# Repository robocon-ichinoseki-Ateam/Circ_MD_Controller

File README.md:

# MD_Controller
VNH5019を駆動させるための回路

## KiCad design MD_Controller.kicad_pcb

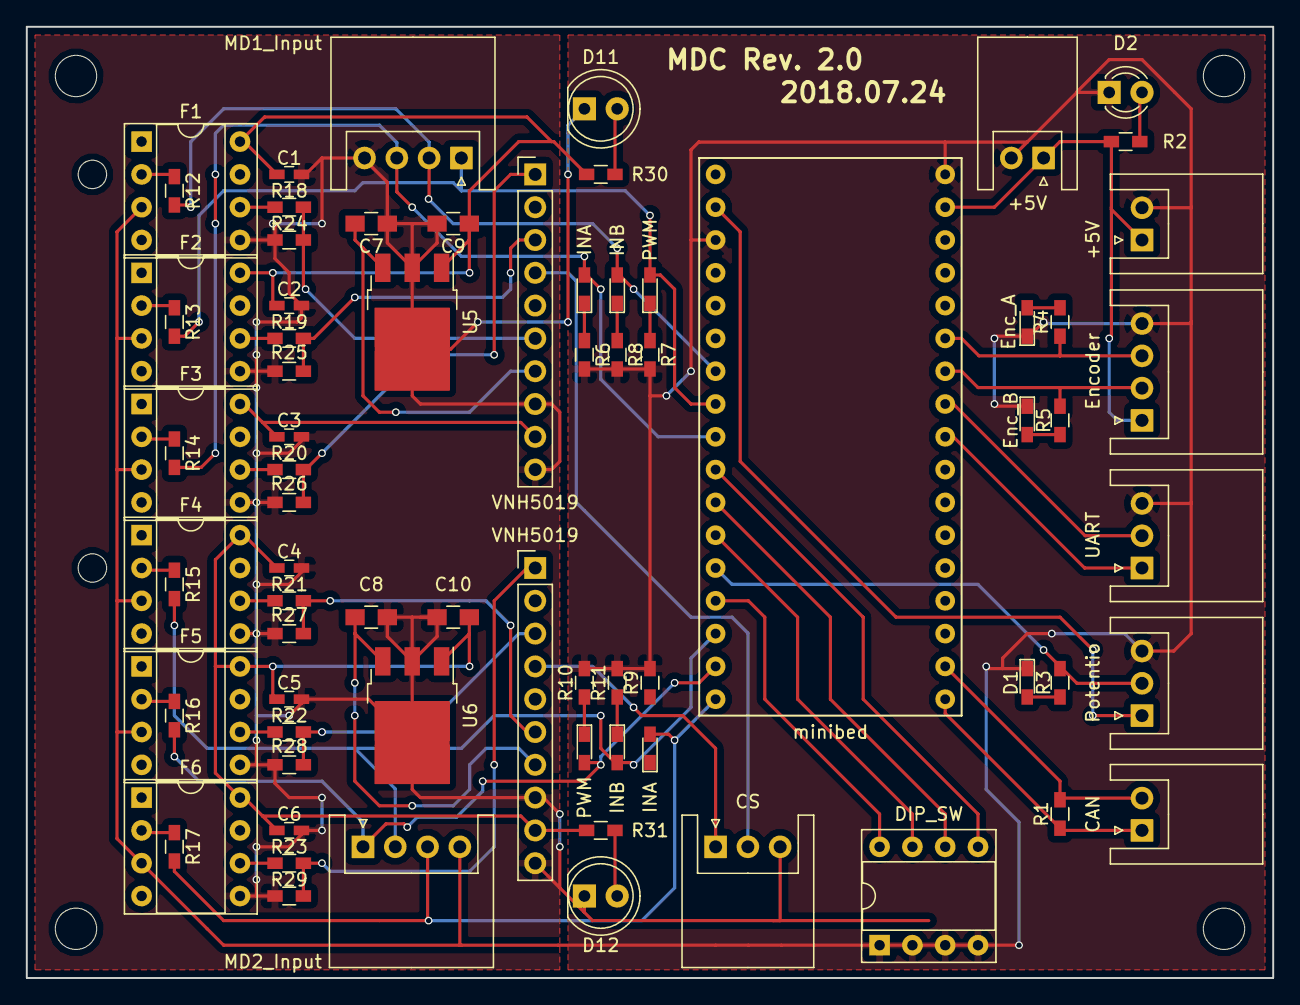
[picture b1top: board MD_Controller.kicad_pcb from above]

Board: 2 copper layers, 96.5 x 73.7 mm, 74 parts (0 on the bottom side), 57 nets.

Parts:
+5V, +5V#2: XH_2; JST_XH_S02B-XH-A_02x2.50mm_Angled
C1, C2, C3, C4, C5, C6: 0.1µF; C_0603_HandSoldering
C7, C8: CP; C_0805_HandSoldering
C9, C10: C; C_0805_HandSoldering
CAN: CAN__connector; JST_XH_S02B-XH-A_02x2.50mm_Angled
CS: XH_3; JST_XH_S03B-XH-A_03x2.50mm_Angled
D1: LED; LED_0603_HandSoldering
D2: LED; LED_D3.0mm_FlatTop
D11, D12: LED; LED_D5.0mm_FlatTop
DIP_SW: dipSW; DIP-8_W7.62mm_Socket
Enc_A: LED; LED_0603_HandSoldering
Enc_B: LED; LED_0603_HandSoldering
Encoder: encoder_connector; JST_XH_S04B-XH-A_04x2.50mm_Angled
F1, F2, F3, F4, F5, F6: TLP250H; DIP-8_W7.62mm_Socket
INA: LED; LED_0603_HandSoldering
INA#2: LED; LED_0603_HandSoldering
INB: LED; LED_0603_HandSoldering
INB#2: LED; LED_0603_HandSoldering
MD1_Input, MD2_Input: XH_4; JST_XH_S04B-XH-A_04x2.50mm_Angled
PWM: LED; LED_0603_HandSoldering
PWM#2: LED; LED_0603_HandSoldering
Potentio: potentio__connector; JST_XH_S03B-XH-A_03x2.50mm_Angled
R1, R2, R3, R4, R5, R6, R7, R8, R9, R10, R11, R12, R13, R14, R15, R16, R17, R18, R19, R20, R21, R22, R23, R24, R25, R26, R27, R28, R29, R30, R31: R; R_0603_HandSoldering
U5, U6: NJM7800SDL1; TO-252-3_TabPin2
UART: XH_3; JST_XH_S03B-XH-A_03x2.50mm_Angled
VNH5019, VNH5019#2: VNH5019; Pin_Header_Straight_1x10_Pitch2.54mm
minibed: minibed

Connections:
+3V3: Potentio.1, minibed.2
+5V: +5V.1, +5V#2.1, Encoder.1, R2.2, minibed.33
CS_1: CS.2, VNH5019.4
CS_2: CS.1, VNH5019#2.4
C_H: CAN.1, R1.1, minibed.18
C_L: CAN.2, R1.2, minibed.19
GND: C1.1, C2.1, C3.1, C4.1, C5.1, C6.1, C7.1, C8.1, C9.2, C10.2, CS.3, D11.1, D12.1, F1.5, F2.5, F3.5, F4.5, F5.5, F6.5, MD1_Input.4, R24.1, R25.1, R26.1, R27.1, R28.1, R29.1, U5.2, U6.2, VNH5019.8, VNH5019.10, VNH5019#2.8, VNH5019#2.10
GNDA: +5V.2, +5V#2.2, D1.1, D2.1, DIP_SW.1, DIP_SW.2, DIP_SW.3, DIP_SW.4, Enc_A.1, Enc_B.1, Encoder.4, F1.3, F2.3, F3.3, F4.3, F5.3, F6.3, MD2_Input.4, Potentio.3, R6.2, R7.2, R8.2, R9.2, R10.2, R11.2, UART.3, minibed.3, minibed.34
INA1: R20.1, R26.2, VNH5019.1
INA2: R23.1, R29.2, VNH5019#2.1
INB1: R18.1, R24.2, VNH5019.6
INB2: R21.1, R27.2, VNH5019#2.6
unnamed: C7.2, U5.3, VNH5019.7
unnamed: C8.2, U6.3, VNH5019#2.7
unnamed: D1.2, R3.2
unnamed: D2.2, R2.1
unnamed: Enc_A.2, R4.2
unnamed: Enc_B.2, R5.2
unnamed: INA.1, R6.1
unnamed: PWM.1, R7.1
unnamed: INB.1, R8.1
unnamed: INA#2.1, R9.1
unnamed: PWM#2.1, R10.1
unnamed: INB#2.1, R11.1
unnamed: D11.2, R30.1
unnamed: D12.2, R31.1
unnamed: F1.2, R12.1
unnamed: F1.6, R18.2
unnamed: F2.2, R13.1
unnamed: F2.6, R19.2
unnamed: F3.2, R14.1
unnamed: F3.6, R20.2
unnamed: F4.2, R15.1
unnamed: F4.6, R21.2
unnamed: F5.2, R16.1
unnamed: F5.6, R22.2
unnamed: F6.2, R17.1
unnamed: F6.6, R23.2
PWM1: R19.1, R25.2, VNH5019.3
PWM2: R22.1, R28.2, VNH5019#2.3
VOUT1: C1.2, C2.2, C3.2, C9.1, F1.8, F2.8, F3.8, R30.2, U5.1, VNH5019.9
VOUT2: C4.2, C5.2, C6.2, C10.1, F4.8, F5.8, F6.8, R31.2, U6.1, VNH5019#2.9
p0: INA.2, MD1_Input.3, R14.2, minibed.9
p1: DIP_SW.5, minibed.10
p2: DIP_SW.6, minibed.11
p3: DIP_SW.7, minibed.12
p5: Potentio.2, R3.1, minibed.13
p6: DIP_SW.8, minibed.14
p7: INB#2.2, MD2_Input.2, R15.2, minibed.15
p8: MD2_Input.1, PWM#2.2, R16.2, minibed.16
p9: INA#2.2, MD2_Input.3, R17.2, minibed.17
p15: UART.1, minibed.26
p17: UART.2, minibed.27
p19: Encoder.2, R5.1, minibed.28
p20: Encoder.3, R4.1, minibed.29
p24: INB.2, MD1_Input.2, R12.2, minibed.7
p25: MD1_Input.1, PWM.2, R13.2, minibed.8

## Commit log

2018-07-10 1.0.0
    これで発注した
2018-07-23 2.0.0
    ネットリストの生成まで終了
2018-07-25 2.1.0
    入力ポートの増設
    電流センサの外部出力ポートの増設
    UARTポートの増設
2018-07-28 2.0.1
    入力ポートの増設
    電流センサの外部出力ポートの増設
    UARTポートの増設
2018-07-28 2.0.2
    発注用ガバーデータの出力
